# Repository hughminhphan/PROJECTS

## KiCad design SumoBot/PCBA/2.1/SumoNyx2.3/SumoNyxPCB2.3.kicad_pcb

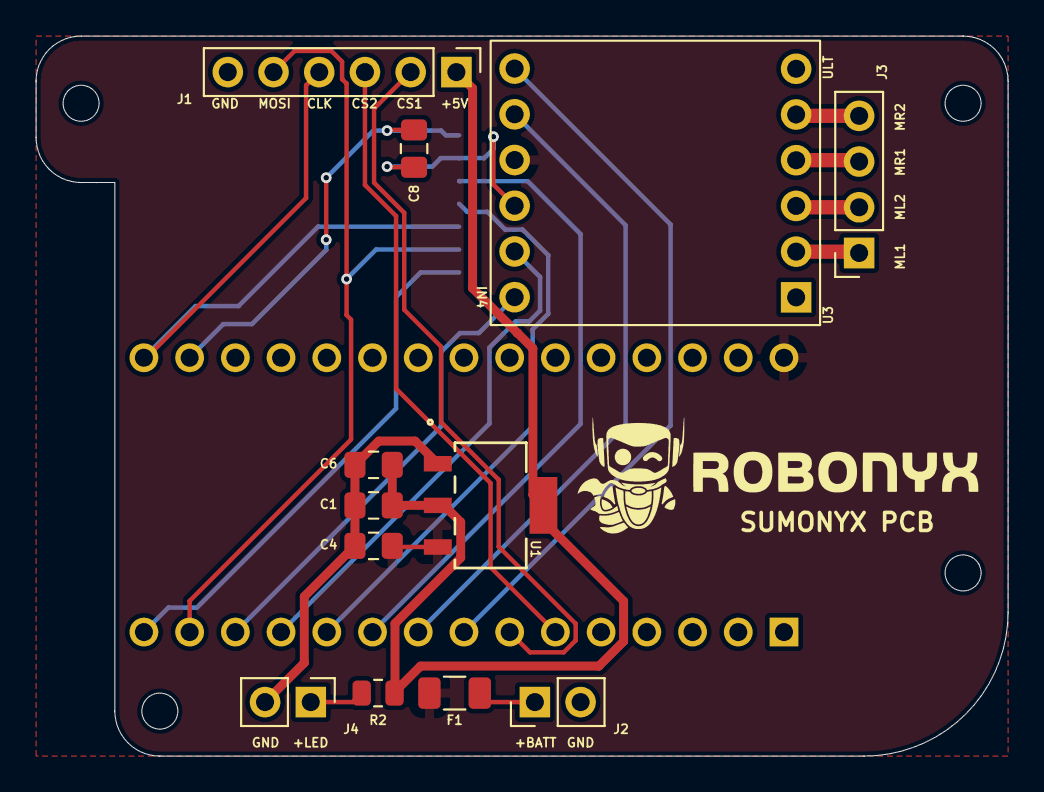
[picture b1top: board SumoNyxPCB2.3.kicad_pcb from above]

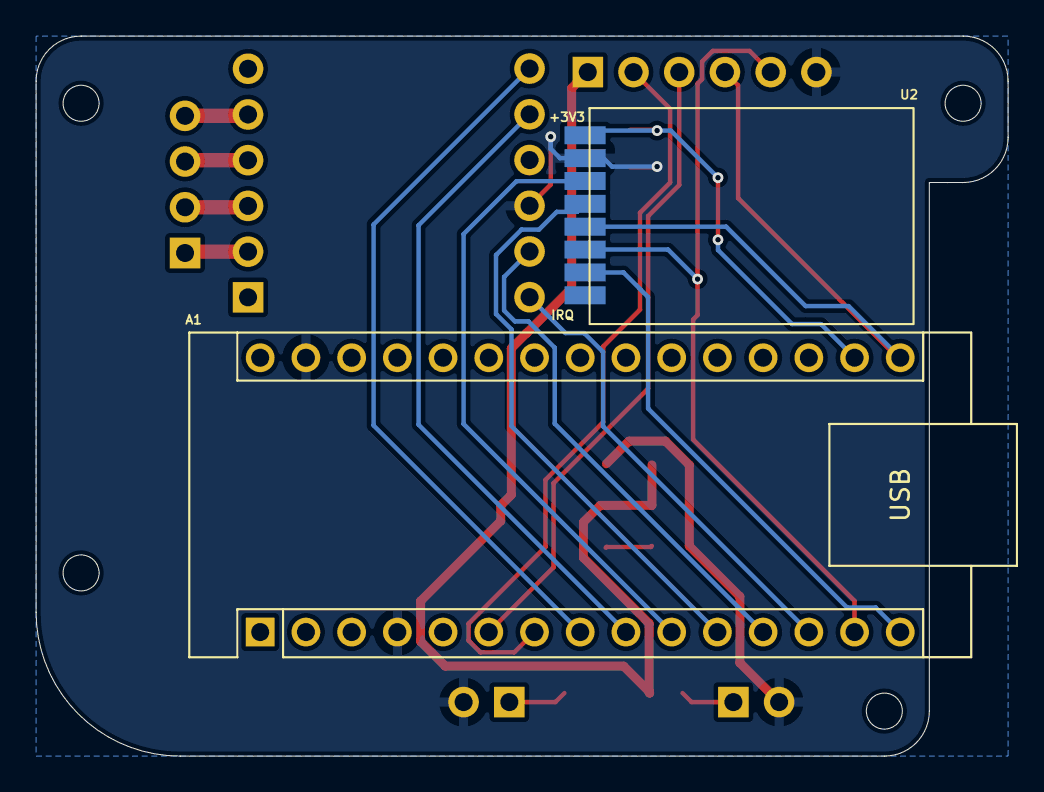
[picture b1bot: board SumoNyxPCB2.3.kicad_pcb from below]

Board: 2 copper layers, 54.0 x 40.0 mm, 14 parts (2 on the bottom side), 21 nets.

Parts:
A1: Arduino_Nano_v3.x; Arduino_Nano
C1, C6: 22UF10V; C_0805_2012Metric_Pad1.18x1.45mm_HandSolder
C4, C8: 10UF10V; C_0805_2012Metric_Pad1.18x1.45mm_HandSolder
F1: SMD1206B110TFT_Polyfuse; Fuse_1206_3216Metric
J1: Conn_01x06_Male; PinHeader_1x06_P2.54mm_Vertical
J2: BATT 7V5; PinHeader_1x02_P2.54mm_Vertical
J3: MOTOR; PinSocket_1x04_P2.54mm_Vertical
J4: BACK 7 LED; PinHeader_1x02_P2.54mm_Vertical
R2: 50R; R_0805_2012Metric
U1: AZ1117IH-5.0TRG1; SOT223-5_DIO
U2: NRF24L01_Breakout; nRF24L01_Breakout_SMD
U3: DRV8833BRKT

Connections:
+3.3V: A1.17 (3V3), C8.2, U2.2 (VCC)
+5V: C1.2, C6.2, J1.1, R2.1, U1.2 (OUTPUT), U1.4 (VOUT)
+7.5V: A1.30 (VIN), C4.2, F1.2, U1.3 (INPUT), U3.10 (VM)
/MOTA1: J3.1, U3.2 (AOUT1)
/MOTA2: J3.2, U3.3 (AOUT2)
/MOTB1: J3.3, U3.4 (BOUT1)
/MOTB2: J3.4, U3.5 (BOUT2)
GND: A1.4 (GND), A1.29 (GND), C1.1, C4.1, C6.1, C8.1, J1.6, J2.2, J4.2, U1.1 (ADJ/GND), U2.1 (GND), U3.9 (GND)
unnamed: A1.6 (D3), J1.3
unnamed: A1.7 (D4), J1.2
unnamed: A1.8 (D5), U3.12 (AIN1)
unnamed: A1.9 (D6), U3.11 (AIN2)
unnamed: A1.10 (D7), U2.3 (CE)
unnamed: A1.11 (D8), U2.4 (~CSN)
unnamed: A1.12 (D9), U3.8 (BIN1)
unnamed: A1.13 (D10), U3.7 (BIN2)
unnamed: A1.14 (D11), J1.5, U2.6 (MOSI)
unnamed: A1.15 (D12), U2.7 (MISO)
unnamed: A1.16 (D13), J1.4, U2.5 (SCK)
unnamed: F1.1, J2.1
unnamed: J4.1, R2.2

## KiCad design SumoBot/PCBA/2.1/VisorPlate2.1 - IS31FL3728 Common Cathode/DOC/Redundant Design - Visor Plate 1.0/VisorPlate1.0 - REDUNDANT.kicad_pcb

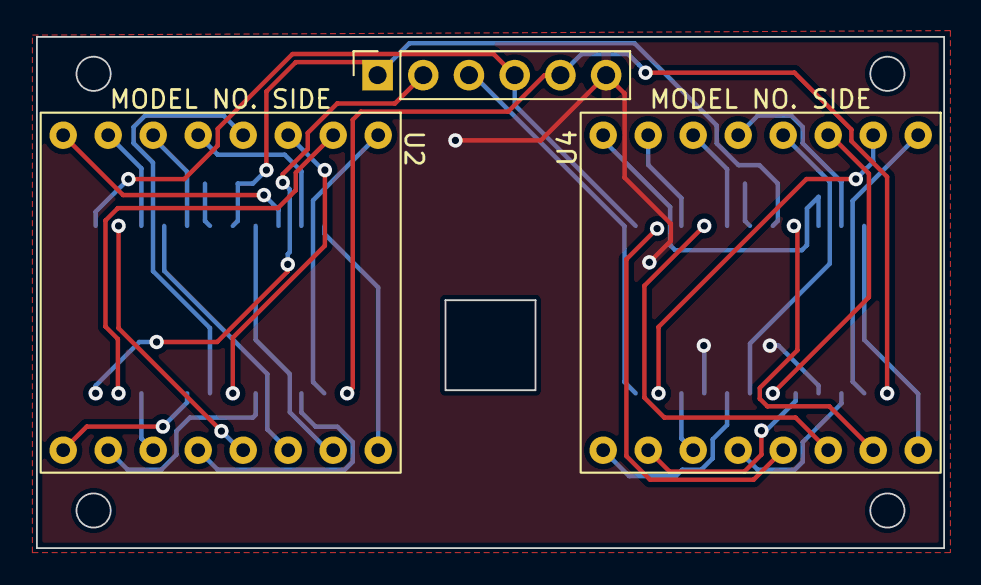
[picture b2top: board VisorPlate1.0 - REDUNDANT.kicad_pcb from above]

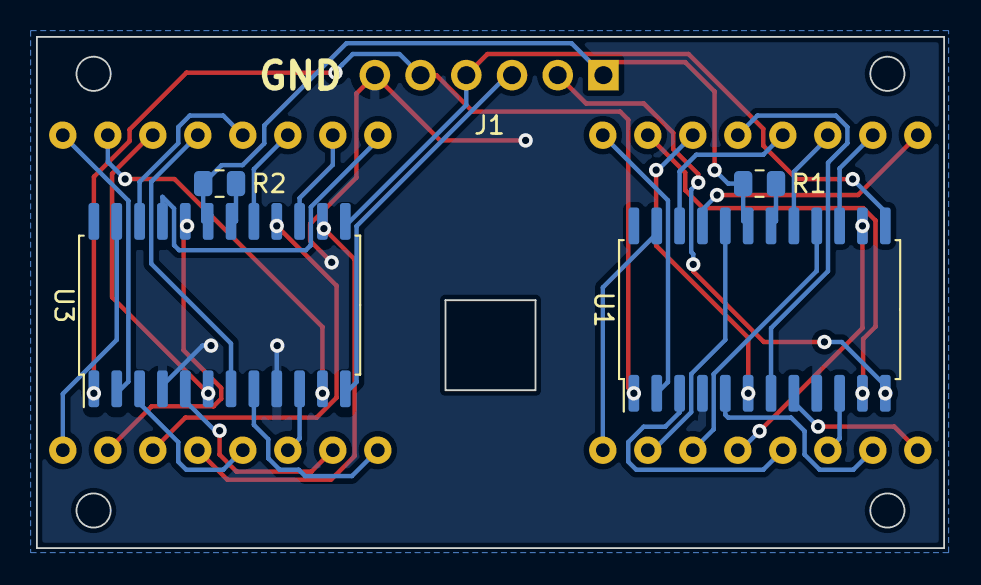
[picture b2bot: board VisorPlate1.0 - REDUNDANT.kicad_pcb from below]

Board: 2 copper layers, 50.4 x 28.4 mm, 7 parts (4 on the bottom side), 40 nets.

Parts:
J1: Conn_01x06_Male; PinSocket_1x06_P2.54mm_Vertical
R1, R2: 24.5k; R_0805_2012Metric
U1, U3: MAX7219; SOIC-24W_7.5x15.4mm_P1.27mm
U2, U4: KWM-20882CBA

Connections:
GND: J1.6, U1.4 (GND), U1.9 (GND), U3.4 (GND), U3.9 (GND)
unnamed: J1.1, R1.2, R2.2, U1.19 (V+), U3.19 (V+)
unnamed: J1.2, U1.12 (LOAD)
unnamed: J1.3, U3.12 (LOAD)
unnamed: J1.4, U1.13 (CLK), U3.13 (CLK)
unnamed: J1.5, U1.1 (DIN), U3.1 (DIN)
unnamed: R1.1, U1.18 (ISET)
unnamed: R2.1, U3.18 (ISET)
unnamed: U1.2 (DIG_0), U2.1
unnamed: U1.3 (DIG_4), U2.12
unnamed: U1.5 (DIG_6), U2.10
unnamed: U1.6 (DIG_2), U2.3
unnamed: U1.7 (DIG_3), U2.4
unnamed: U1.8 (DIG_7), U2.9
unnamed: U1.10 (DIG_5), U2.11
unnamed: U1.11 (DIG_1), U2.2
unnamed: U1.14 (SEG_A), U2.13
unnamed: U1.15 (SEG_F), U2.7
unnamed: U1.16 (SEG_B), U2.14
unnamed: U1.17 (SEG_G), U2.6
unnamed: U1.20 (SEG_C), U2.15
unnamed: U1.21 (SEG_E), U2.8
unnamed: U1.22 (SEG_DP), U2.5
unnamed: U1.23 (SEG_D), U2.16
unnamed: U3.2 (DIG_0), U4.1
unnamed: U3.3 (DIG_4), U4.12
unnamed: U3.5 (DIG_6), U4.10
unnamed: U3.6 (DIG_2), U4.3
unnamed: U3.7 (DIG_3), U4.4
unnamed: U3.8 (DIG_7), U4.9
unnamed: U3.10 (DIG_5), U4.11
unnamed: U3.11 (DIG_1), U4.2
unnamed: U3.14 (SEG_A), U4.13
unnamed: U3.15 (SEG_F), U4.7
unnamed: U3.16 (SEG_B), U4.14
unnamed: U3.17 (SEG_G), U4.6
unnamed: U3.20 (SEG_C), U4.15
unnamed: U3.21 (SEG_E), U4.8
unnamed: U3.22 (SEG_DP), U4.5
unnamed: U3.23 (SEG_D), U4.16

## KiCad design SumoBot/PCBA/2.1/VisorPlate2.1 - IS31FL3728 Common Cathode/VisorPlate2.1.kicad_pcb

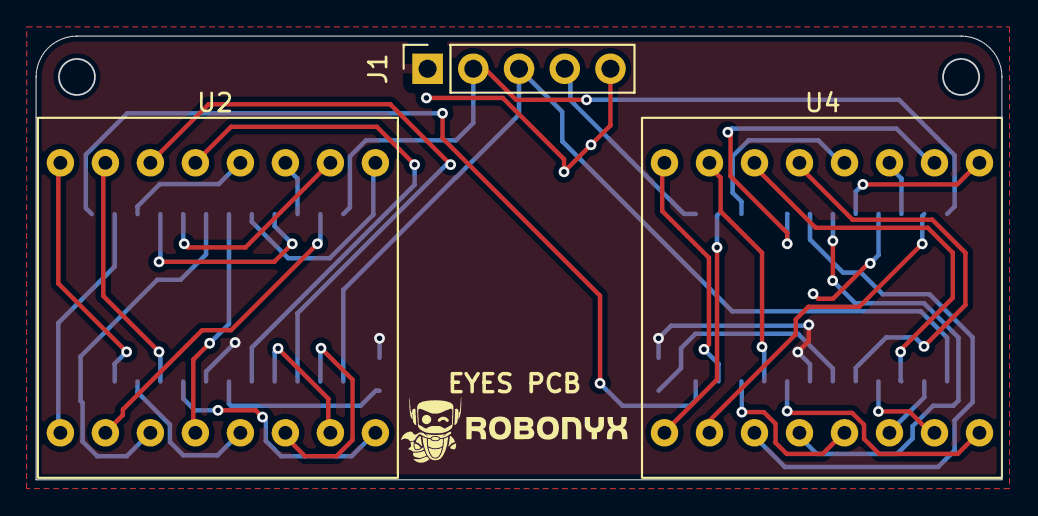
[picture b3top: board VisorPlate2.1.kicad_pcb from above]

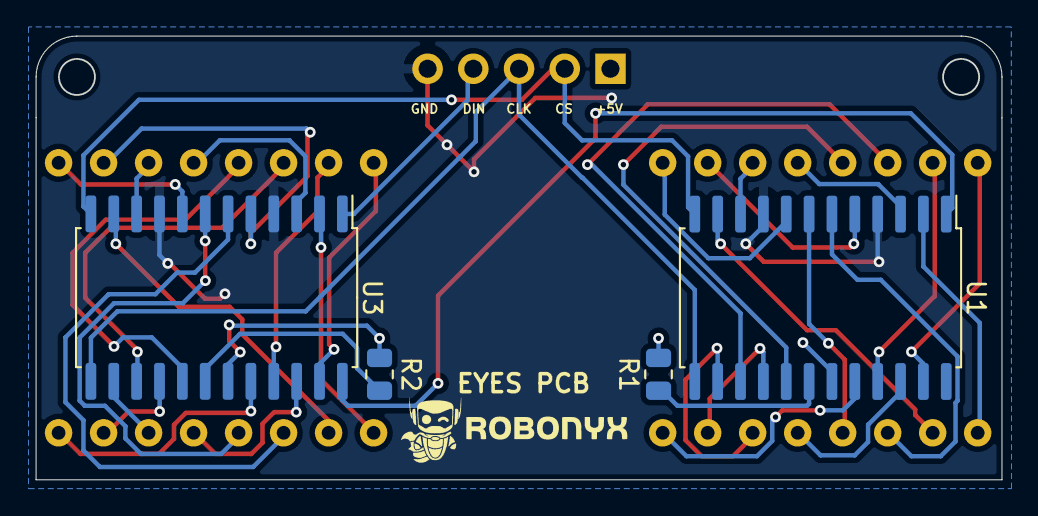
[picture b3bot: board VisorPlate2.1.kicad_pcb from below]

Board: 2 copper layers, 53.7 x 24.7 mm, 7 parts (4 on the bottom side), 40 nets.

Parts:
J1: Conn_01x05_Male; PinSocket_1x05_P2.54mm_Vertical
R1, R2: 27K; R_0805_2012Metric
U1, U3: MAX7219; SOIC-24W_7.5x15.4mm_P1.27mm
U2, U4: KWM-20882CBA

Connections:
/+5V: J1.1, R1.2, R2.2, U1.19 (V+), U3.19 (V+)
/CLK: J1.3, U1.13 (CLK), U3.13 (CLK)
/CS2: J1.2, U1.12 (LOAD), U3.12 (LOAD)
/DIN: J1.4, U3.1 (DIN)
GND: J1.5, U1.4 (GND), U1.9 (GND), U3.4 (GND), U3.9 (GND)
unnamed: R1.1, U1.18 (ISET)
unnamed: R2.1, U3.18 (ISET)
unnamed: U1.1 (DIN), U3.24 (DOUT)
unnamed: U1.2 (DIG_0), U2.9
unnamed: U1.3 (DIG_4), U2.4
unnamed: U1.5 (DIG_6), U2.2
unnamed: U1.6 (DIG_2), U2.11
unnamed: U1.7 (DIG_3), U2.12
unnamed: U1.8 (DIG_7), U2.1
unnamed: U1.10 (DIG_5), U2.3
unnamed: U1.11 (DIG_1), U2.10
unnamed: U1.14 (SEG_A), U2.14
unnamed: U1.15 (SEG_F), U2.6
unnamed: U1.16 (SEG_B), U2.15
unnamed: U1.17 (SEG_G), U2.5
unnamed: U1.20 (SEG_C), U2.16
unnamed: U1.21 (SEG_E), U2.7
unnamed: U1.22 (SEG_DP), U2.13
unnamed: U1.23 (SEG_D), U2.8
unnamed: U3.2 (DIG_0), U4.9
unnamed: U3.3 (DIG_4), U4.4
unnamed: U3.5 (DIG_6), U4.2
unnamed: U3.6 (DIG_2), U4.11
unnamed: U3.7 (DIG_3), U4.12
unnamed: U3.8 (DIG_7), U4.1
unnamed: U3.10 (DIG_5), U4.3
unnamed: U3.11 (DIG_1), U4.10
unnamed: U3.14 (SEG_A), U4.14
unnamed: U3.15 (SEG_F), U4.6
unnamed: U3.16 (SEG_B), U4.15
unnamed: U3.17 (SEG_G), U4.5
unnamed: U3.20 (SEG_C), U4.16
unnamed: U3.21 (SEG_E), U4.7
unnamed: U3.22 (SEG_DP), U4.13
unnamed: U3.23 (SEG_D), U4.8
